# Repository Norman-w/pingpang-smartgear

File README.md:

# 乒乓智配 · PingPang SmartGear

乒乓球训练与比赛相关的智能辅助装备、配件及识别系统。

## 裸激光可调夹座首样

新增左侧十路裸激光方案：每颗光头装入独立球面夹筒，以两颗斜向螺钉微调，整排沿用原球头粗调。调整时从头套编号孔进入，邻近光头和盖件保持安装；预览页提供[原位调节演示与夹座特写](hardware/cad/preview/?view=laser)。尺寸暂按 Ø6×12 mm，实体适配和光路精度待实测。

设计、装配和独立 STL 包见[小夹座说明](docs/laser-micro-mount-v0.1.zh-CN.md)。前盖已加深、加宽并恢复完整弧形侧壁；新前后盖、承载条、底盖及底部柔性垫配套使用。预览支持围绕鼠标缩放和各倍率下平移。下文原 M6 电子与打印资料保留作参考，不表示其电路已经适配裸激光。

[接收端配套外壳](docs/receiver-mount-v0.1.zh-CN.md)也已同步扩大，提供独立五件打印包和右侧特写；内部接收元件选择尚未确认。

## 当前项目

当前机械主线是一套免打孔的内置式球网支架：左右夹体固定在球台边缘，网布直接装入两侧立柱，网端附近各有一个 PVDF 振动传感器；左右各十路 M6 发射/接收器件用于过网高度/事件采集，电子系统由 ESP32-S3 主控和独立 M6 接收载板组成。

当前阶段已经完成：

- OpenSCAD 统一机械参数源、完整装配、爆炸和真实截面诊断；
- C 形夹按 y=0 分型为两半；承载发射/接收头的斜立柱另分为下段和顶部 `30 mm` 上段，分型处用公母定位键和四枚 M3×40 连接；网布侧边使用独立圆柱插杆，不再使用外侧矩形网夹；立柱从黄灰交界 `z=16 mm` 延伸至 `z=260.5 mm`，不向下插入 C 形座；网布/圆柱插杆功能区仍为 `z=16…168.5 mm`；
- 网布的 `3 mm` 过道，以及球网空心边套和 `Ø10 mm` 圆柱插杆；插杆先穿过网布边套，再沿原门洞轴线从 x 侧推入下段侧开接收腔，门洞宽度保持历史 `15.2 mm`，立柱分型位于顶部下 `30 mm`，网顶不设置轨道；
- ESP32 主控、电池、电源保护、接收/发射/UI 子板的 KiCad/Atopile 交接包；
- 板框、安装孔、梯形腔、y+ 一体式 UI 填平固定板和电子件的统一 fit report；
- 当前 `41` 个正式机械 STL，以及 `256 mm` 打印床 `7` 张板、`41` 件、`0` 件超尺寸的几何拼盘；斜立柱下段/绿色载体采用实际三轴斜放，上段按平放姿态打印。

仍未由文件替代的工作包括：PCB 铜箔/器件生产释放和电气波形、真实网布与 M6 SKU 实测、立柱与 C 夹的打印配合及 PETG 承力、盒盖实际贴合、切片/G-code、首层和实物装配联调。

网端安装规则：先把球网侧边空心布套套到一根 `Ø10 mm × 152.5 mm` 圆柱插杆上，再沿原门洞轴线从 x 侧推入下段侧开接收腔，最后安装上段把插杆封在立柱内；拆卸按相反顺序进行。固定 C 夹两半除网布过道外保持实心，立柱底面与 `z=16 mm` 黄灰交界共面，分型在顶部下 `30 mm`，上段与下段用公母键和四枚 M3×40 连接；下段从承托面起做 `35×58 mm → 28×38 mm` 连续实心渐变，以上保持 `28×38 mm`。

这里的“齐平”仅表示一体式 UI 填平固定板和 M6 盖件装配后没有明显错台或松动，不宣称 IP 防水等级。

## 仓库结构

```text
docs/       需求、技术方案、测量定义和测试记录
hardware/   机械 CAD、电子板、BOM、打印和装配资料
firmware/   设备控制器、传感器采集和通信固件
vision/     球体检测、轨迹估计、过网高度计算
software/   标定工具、调试界面和训练/比赛数据接口
```

## 入口文档

- [硬件工程说明](hardware/README.md)
- [OpenSCAD 机械主线](hardware/cad/README.md)
- [打印清单](hardware/cad/print-manifest.zh-CN.md)
- [ESP32 主控与 1S 电源首样板](hardware/electronics/esp32-control-v0.1/README.zh-CN.md)
- [统一电子系统干涉/打印自证报告](hardware/electronics/fit-report-v0.2.md)
- [Atopile 系统接口合同](hardware/electronics/atopile/README.zh-CN.md)
- [系统机械—电气接口合同](hardware/electronics/system-packaging-v0.2.zh-CN.md)
- [M6 阵列设计说明](docs/m6-optical-array-design-v0.1.zh-CN.md)
- [首样采购与装配清单](hardware/first-article-bom.zh-CN.md)

## 设计原则

1. 先建立可测量、可追溯的机械和高度基准。
2. 机械、电子和识别链路分层，任何一层未实测时保持 `pending/unknown`。
3. 以装配、干涉、通道数量和实物波形共同放行，不以“能编译”代替接板通过。
4. 所有打印包必须能追溯到参数源、清单、包围盒和封闭拓扑摘要。

本项目当前面向训练、实验和产品研发；未经重复性、环境适应性和规则符合性验证的版本，不作为正式比赛裁判依据。

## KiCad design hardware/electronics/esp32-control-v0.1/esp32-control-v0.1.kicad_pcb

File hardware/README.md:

# 硬件工程

这里放置内置式球网支架、两侧 M6 发射/接收阵列、网端 PVDF 传感器、ESP32 主控、子板、电池和装配资料。

新增的左侧裸激光可调小夹座见[结构与装配说明](../docs/laser-micro-mount-v0.1.zh-CN.md)。单颗特写、原位调节演示与整排共用 SCAD 导出的模型，工具从编号孔进入，邻居和后盖保持固定。输出位于 `cad/exports/laser-micro-mount-v0.1/`；加大前腔的新前盖、新承载条、后盖、底盖与底部柔性垫成套使用，原 M6 电气资料仅供接口参考。

右侧也已同步[接收端外壳](../docs/receiver-mount-v0.1.zh-CN.md)，输出为 `cad/exports/receiver-mount-v0.1/`；内部元件仍为原M6接口参考，待确认接收器后适配固定座。

## 当前硬件拆分

- [`cad/`](cad/)：参数化 OpenSCAD 机械源、完整装配/爆炸/剖切预览、正式 STL 导出和 256 mm 打印拼盘；
- [`electronics/`](electronics/)：ESP32-S3 主控板、M6 接收载板、发射端内置电源子板、UI 子板、Atopile 接口合同、3D 板模型和统一壳内干涉报告；
- [`first-article-bom.zh-CN.md`](first-article-bom.zh-CN.md)：首样采购和实物放行边界；
- [`../docs/m6-optical-array-design-v0.1.zh-CN.md`](../docs/m6-optical-array-design-v0.1.zh-CN.md)：M6 阵列和安装基准。

电子系统的机械—电气合同见 [`electronics/system-packaging-v0.2.zh-CN.md`](electronics/system-packaging-v0.2.zh-CN.md)。其中已给出母板、接收/发射/UI 子板、端子化线束、电池仓、USB-C、按钮、屏幕预留、扬声器/蜂鸣器、指示灯和梯形腔的统一坐标。主控与 1S 电源首样板见 [`electronics/esp32-control-v0.1/`](electronics/esp32-control-v0.1/)，M6 接收载板和发射端电源子板见 [`electronics/daughter-boards-v0.2/`](electronics/daughter-boards-v0.2/)。

## 当前机械结构

网顶不设置轨道。网布侧边空心布套先套到 `Ø10 mm × 152.5 mm` 圆柱插杆，再把这套组件从球台中心侧穿过立柱下段的连续 `3 mm` 网布过道，沿原门洞轴线从 x 侧推入下段的侧开接收腔；安装上段后封住插入口。斜立柱在顶部下 `30 mm` 分成下段和可替换上段，两段用公母定位键和四枚 M3×40 自攻钉连接。网端附近左右各一个 PVDF 振动传感器，与网架保留 `18 mm` 横向净距。

C 形夹按 y=0 分型为 `clamp_body_half_user` 与 `clamp_body_half_opponent` 两半，斜立柱和绿色载体则由 `post_clamp_carrier_lower`、`post_clamp_carrier_upper` 两件打印；固定夹半体除网布 `3 mm` 过道和侧开接收腔外保持实心。立柱底面在 C 夹黄灰交界 `z=16 mm` 共面，分型位于顶部下 `30 mm`，上段带公母键、四枚 M3×40 连接孔和中心 M8×1.25 攻丝座；网布/圆柱插杆功能区仍只到 `z=168.5 mm`。网端装配不使用矩形卡夹、keeper 或竖直盲孔：先把边套套在 Ø10 圆柱上，再沿 x 方向推入下段侧开接收腔，最后合上上段。球头下端直接拧入上段中心座，四枚立柱连接螺丝只属于立柱上下段。

盒盖、压合边和接口以“装配后严丝合缝、无明显贯穿缝”为目标；这里不宣称防水等级。真实网布、螺纹、张力、线缆弯曲和夹体耐久必须用首样实测。

## 打印状态

当前正式机械包以 [`cad/print-manifest.zh-CN.md`](cad/print-manifest.zh-CN.md) 和 [`cad/exports/desktop-clamp-one-side-x1c-v0.7-split-c-scheme/manifest.json`](cad/exports/desktop-clamp-one-side-x1c-v0.7-split-c-scheme/manifest.json) 为准：`41` 个 STL。256 mm 打印床拼盘见 [`cad/exports/desktop-clamp-one-side-x1c-v0.7-split-c-scheme/print-platter-256/manifest.json`](cad/exports/desktop-clamp-one-side-x1c-v0.7-split-c-scheme/print-platter-256/manifest.json)：`7` 张板、`41` 个已排版、`0` 个超尺寸件；斜立柱下段/绿色载体使用实际三轴斜放，上段按分型面平放姿态打印。旧整高 C 夹、电子腔底盖/连续垫、网夹分体、套筒和内芯不再属于当前清单；旧矩形卡条与 keeper 已移除，当前为独立 Ø10 mm 圆柱插杆和下段侧开接收腔。

立柱上下段连接螺丝当前按普通盘头或低矮圆头 `M3×40` 自攻钉采购；结构没有 90° 沉头窝，也不使用台阶肩螺丝。这是 CAD 包络/封闭 STL/排版证据，不是已切片、已生成 G-code 或已完成实物打印的证明。

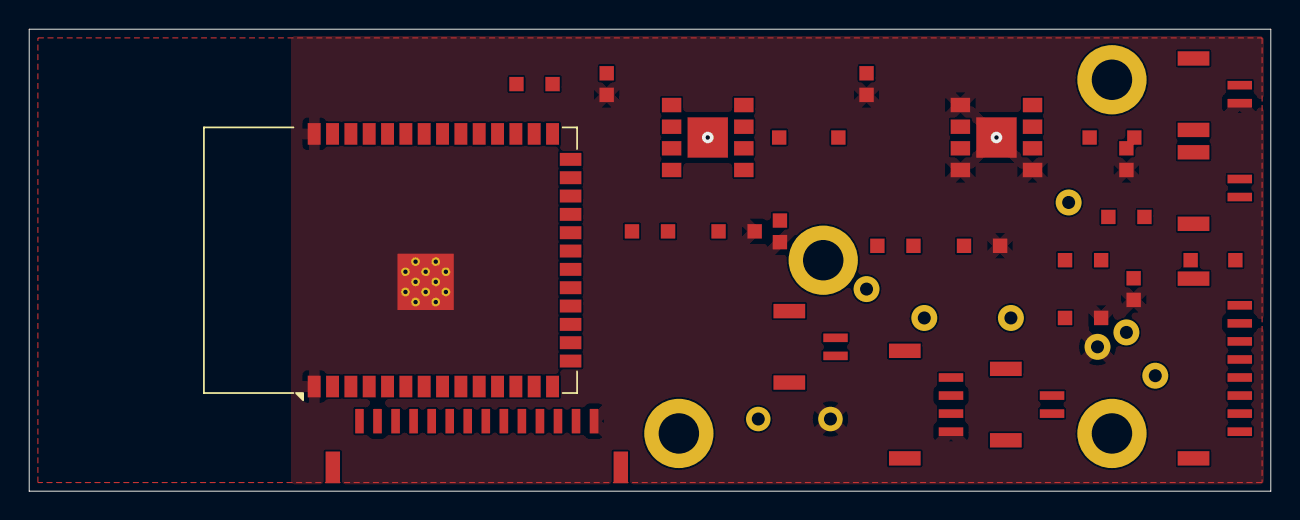
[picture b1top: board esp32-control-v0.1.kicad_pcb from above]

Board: 2 copper layers, 86.0 x 32.0 mm, 38 parts (0 on the bottom side), 34 nets, no tracks yet.

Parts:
C1: 100n BAT_SENSE
C2: 22u BAT
C3: 10u VBUS
C4: 22u SYS5V
C5: 10u 3V3
C6: 100n BUCK_EN
D1: GREEN STATUS
D2: TVS 33V SENSOR
F1: PTC 1.1A
F2: PTC SENSOR
H1, H2, H3, H4: M2.5 NPTH
J2: MX1.25_PROTECTED_1S_BAT
J3: MX1.25_SENSOR_10-30V_IN
J4: MX1.25_M6_CARRIER_HOST
J5: MX1.25_PVDF_ADC_AUX
J6: MX1.25_PVDF_CMP_AUX_DNP
J7: MX1.25_UI_PANEL_LOCK_14P_CHARGE
J8: MX1.25_M6_SENSOR_RAIL_LINK
L1: 2.2uH BOOST XFL4020
L2: 2.2uH BUCK XFL3012
R5: 1M BAT_TOP
R6: 1M BAT_BOTTOM
R7: 100k BUCK_EN
R8: 1k CHARGE_LED
SW1: IP5305 KEY
TP1, TP2, TP3, TP4, TP5, TP6, TP7: TEST_POINT
U1: ESP32-S3-WROOM-1-N16R8; ESP32-S3-WROOM-1
U2: IP5305T-HSOP8-1EP
U3: TPS62162-QFN8-EP

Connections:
3v3: C5.1, J4.1, J7.1, L2.2, TP4.1, U1.2, U3.6
bat_p: C2.1, J2.1, R5.1, TP1.1, U2.6
bat_sense: C1.1, R5.2, R6.1, TP2.1, U1.17
boost_sw: L1.1, U2.7
buck_en: C6.1, R7.2, U3.3
buck_sw: L2.1, U3.7
carrier_cs_n: J4.6, U1.21
carrier_irq_n: J4.7, TP6.1, U1.22
carrier_miso: J4.5, U1.20
carrier_mosi: J4.4, U1.19
carrier_reset_n: J4.8, U1.5
carrier_sck: J4.3, U1.18
gnd: C1.2, C2.2, C3.2, C4.2, C5.2, C6.2, D1.2, J2.2, J4.2, J5.2, J5.4, J7.2, J7.14, R6.2, SW1.2, TP5.1, U1.1, U1.40, U1.41, U2.9, U3.1, U3.4, U3.5, U3.9
led_charge: R8.1, U2.2
power_key: SW1.1, U2.5
pvdf_adc_l: J5.1, U1.39
pvdf_adc_r: J5.3, U1.38
sensor_ext: F2.1, J3.1
sensor_fused: D2.1, F2.2, J8.1, TP7.1
sensor_gnd: D2.2, J3.2, J8.2
status_led: D1.1, R8.2
sys_5v: C4.1, L1.2, R7.1, TP3.1, U2.8, U3.2
ui_btn_mode: J7.6, U1.4
ui_btn_start: J7.5, U1.16
ui_buzzer: J7.7, U1.13
ui_led_battery: J7.12, U1.23
ui_led_status: J7.11, U1.12
ui_scl: J7.4, U1.9
ui_sda: J7.3, U1.10
ui_spk_bclk: J7.8, U1.7
ui_spk_dout: J7.10, U1.11
ui_spk_ws: J7.9, U1.8
usb_vbus: F1.1, J7.13
vbus_limited: C3.1, F1.2, U2.1

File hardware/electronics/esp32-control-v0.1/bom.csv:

ref,qty,value,role,status,notes
U1,1,ESP32-S3-WROOM-1-N16R8,主控,候选,按模块官方 land pattern 与 N16R8 OPI 限制复核
U2,1,IP5305T-HSOP8-1EP,1S 充电/5V 升压,候选,按现有 SmartPaddle 电源架构复核 VIN/BAT/SW/VOUT/EP
U3,1,TPS62162-QFN8-EP,3V3 降压,候选,固定 3.3V；FB 接地；PG 保留测试点
J2,1,MX1.25_PROTECTED_1S_LOCK_2P,受保护 1S 电池,候选,物理节距锁定 1.25 mm；禁止裸电芯；确认极性与线束防呆
J3,1,MX1.25_SENSOR_10-30V_IN,外部 M6 电源,首样,物理节距锁定 1.25 mm；pin2 为 sensor_gnd/0V_SENSOR，与 MCU GND 分离
J4,1,MX1.25_M6_CARRIER_HOST_8P,STM32G031 载板,接口已落板,物理节距锁定 1.25 mm；3V3/GND/SCK/MOSI/MISO/CS/IRQ/RESET
J5,1,MX1.25_PVDF_ADC_AUX_4P,PVDF ADC,辅助,物理节距锁定 1.25 mm；GPIO1/2；AFE 仍待设计
J6,1,MX1.25_PVDF_CMP_AUX_DNP_2P,PVDF 比较器辅助,不装,物理节距锁定 1.25 mm；GPIO14 给载板 IRQ；避免隐式复用
J7,1,MX1.25_UI_PANEL_LOCK_14P_CHARGE,UI 子板 14 芯对插,候选,物理节距锁定 1.25 mm；1-12 为 UI 控制，13/14 为 Type-C VBUS/GND；按真实锁扣座核对
J8,1,MX1.25_M6_SENSOR_RAIL_LINK_2P,接收载板传感器电源,候选,物理节距锁定 1.25 mm；pin1/pin2 映射 sensor_fused/sensor_gnd 到接收载板 J_PWR
F1,1,PTC 1.1A,UI Type-C 充电输入限流,候选,实测 UI 面板 Type-C 输入峰值和温升
F2,1,PTC SENSOR,传感器电源保护,候选,电流按 M6 实物确认
D2,1,TVS 33V SENSOR,传感器电源 TVS,候选,型号随外部 10–30V 瞬态记录冻结
L1,1,2.2uH BOOST XFL4020,IP5305T 升压电感,候选,按 U2 推荐布局/饱和电流复核
L2,1,2.2uH BUCK XFL3012,TPS62162 降压电感,候选,按 U3 推荐布局/电流复核
R5,1,1M BAT_TOP,电池分压上臂,候选,GPIO9 sense
R6,1,1M BAT_BOTTOM,电池分压下臂,候选,GPIO9 sense
R7,1,100k BUCK_EN,降压使能上拉,候选,与 C6 形成首样启动控制
R8,1,1k CHARGE_LED,充电指示限流,候选,LED 电流实测
C1,1,100n BAT_SENSE,电池采样滤波,候选,靠近 ESP32 ADC
C2,1,22u BAT,电池去耦,候选,按 IP5305T 推荐值复核
C3,1,10u VBUS,输入去耦,候选,靠近 U2 VIN
C4,1,22u SYS5V,升压输出去耦,候选,靠近 U2 VOUT
C5,1,10u 3V3,3V3 输出去耦,候选,靠近 U3/ESP32
C6,1,100n BUCK_EN,使能滤波,候选,按 EN 启动波形复核
D1,1,GREEN STATUS,充电/电源指示,候选,LED1 路径
SW1,1,IP5305 KEY,电源按键,候选,确认 IP5305T KEY 时序

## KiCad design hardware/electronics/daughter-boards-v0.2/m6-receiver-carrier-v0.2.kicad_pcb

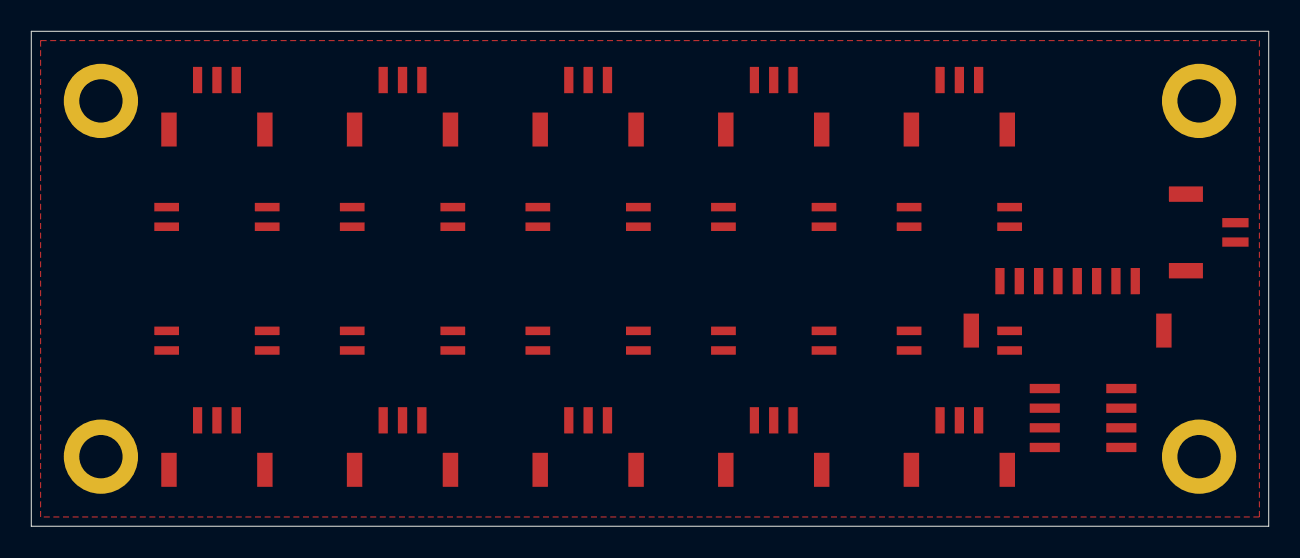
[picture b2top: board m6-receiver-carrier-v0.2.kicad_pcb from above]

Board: 2 copper layers, 80.0 x 32.0 mm, 27 parts (0 on the bottom side), 28 nets, no tracks yet.

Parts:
H1, H2, H3, H4: M2.5 NPTH
J_HOST: MX1.25_MOTHER_HOST_LOCK_8P
J_PWR: MX1.25_SENSOR_RAIL_LOCK_2P
J_RX00, J_RX01, J_RX02, J_RX03, J_RX04, J_RX05, J_RX06, J_RX07, J_RX08, J_RX09: MX1.25_LOCK_3P_RX
U_MCU: STM32G031_PLACEHOLDER
U_OP00, U_OP01, U_OP02, U_OP03, U_OP04, U_OP05, U_OP06, U_OP07, U_OP08, U_OP09: OPTO_PLACEHOLDER

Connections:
3v3: J_HOST.1, U_MCU.7, U_OP00.3, U_OP01.3, U_OP02.3, U_OP03.3, U_OP04.3, U_OP05.3, U_OP06.3, U_OP07.3, U_OP08.3, U_OP09.3
carrier_cs_n: J_HOST.6, U_MCU.4
carrier_irq_n: J_HOST.7, U_MCU.5
carrier_miso: J_HOST.5, U_MCU.3
carrier_mosi: J_HOST.4, U_MCU.2
carrier_reset_n: J_HOST.8, U_MCU.6
carrier_sck: J_HOST.3, U_MCU.1
gnd: J_HOST.2, U_MCU.8, U_OP00.4, U_OP01.4, U_OP02.4, U_OP03.4, U_OP04.4, U_OP05.4, U_OP06.4, U_OP07.4, U_OP08.4, U_OP09.4
rx00_gnd: J_RX00.2, U_OP00.2
rx00_sig: J_RX00.3, U_OP00.1
rx01_gnd: J_RX01.2, U_OP01.2
rx01_sig: J_RX01.3, U_OP01.1
rx02_gnd: J_RX02.2, U_OP02.2
rx02_sig: J_RX02.3, U_OP02.1
rx03_gnd: J_RX03.2, U_OP03.2
rx03_sig: J_RX03.3, U_OP03.1
rx04_gnd: J_RX04.2, U_OP04.2
rx04_sig: J_RX04.3, U_OP04.1
rx05_gnd: J_RX05.2, U_OP05.2
rx05_sig: J_RX05.3, U_OP05.1
rx06_gnd: J_RX06.2, U_OP06.2
rx06_sig: J_RX06.3, U_OP06.1
rx07_gnd: J_RX07.2, U_OP07.2
rx07_sig: J_RX07.3, U_OP07.1
rx08_gnd: J_RX08.2, U_OP08.2
rx08_sig: J_RX08.3, U_OP08.1
rx09_gnd: J_RX09.2, U_OP09.2
rx09_sig: J_RX09.3, U_OP09.1

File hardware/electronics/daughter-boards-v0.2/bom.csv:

board,ref,qty,value,role,status,notes
m6-receiver-carrier-v0.2,U_OP00..U_OP09,10,opto-isolator + input resistor,十路 NPN 隔离前端,候选,按 M6 输出极性/电流和 STM32 输入阈值冻结
m6-receiver-carrier-v0.2,J_RX00..J_RX09,10,MX1.25_LOCK_3P_RX,十路接收器三芯对插,候选,线束汇聚后插入；按线径和插拔空间核对真实 MX1.25 封装
m6-receiver-carrier-v0.2,J_HOST,1,MX1.25_MOTHER_HOST_LOCK_8P,母板逻辑接口,候选,3V3/GND/SPI/IRQ/RESET；物理节距锁定 1.25 mm
m6-receiver-carrier-v0.2,J_PWR,1,MX1.25_SENSOR_RAIL_LOCK_2P,接收器外部电源接口,候选,与母板逻辑线分开；物理节距锁定 1.25 mm
m6-receiver-carrier-v0.2,U_MCU,1,STM32G031_PLACEHOLDER,十路边沿采集 MCU,候选,占位封装；最终按独立载板方案冻结
emitter-power-v0.2,J_BAT,1,MX1.25_PROTECTED_1S_LOCK_2P,内置受保护 1S 电池接口,候选,物理节距锁定 1.25 mm；禁止裸电芯；需防呆/锁扣
emitter-power-v0.2,J_EXT,1,MX1.25_EXT_TX_10-30V_2P_CURRENT_GATE,发射端外接后备电源,候选,MX1.25 物理接口；额定电流/端子温升仍需核对，不与电池裸并联
emitter-power-v0.2,U_BOOST,1,TX_BOOST_CURRENT_RATED_PLACEHOLDER,发射端升压/限流,候选,按十路同时点亮电流和温升冻结
emitter-power-v0.2,F_TX,1,PTC_OR_FUSE,发射端过流保护,候选,按内置电池/外部输入分别核算
emitter-power-v0.2,D_TVS,1,TVS_BY_MODULE,发射端输入瞬态保护,候选,外部输入路径按 10–30 V 边界复核
emitter-power-v0.2,J_TX_A/J_TX_B,2,MX1.25_TX_A/B_10P,十路发射器两芯线束,候选,TX00..TX04 与 TX05..TX09 各 10 芯；不使用 2.54 mm 或错误 1.27 mm 20P 模型
ui-panel-v0.2,J_MOTHER,1,MX1.25_MOTHER_UI_LOCK_14P_CHARGE,母板 UI 对插,候选,物理节距锁定 1.25 mm；13/14 脚带回 Type-C VBUS/GND；核对真实锁扣座
ui-panel-v0.2,J_OLED,1,MX1.25_I2C_OLED_FPC_4P,0.96 英寸 OLED 排线接口,候选,屏幕独立安装；物理节距锁定 1.25 mm；盖板透明窗/压框
ui-panel-v0.2,SW_START/SW_MODE,2,SW_SPST_TS-1088-xR020,PCB 直装 START/MODE 贴片按键,候选,3.9×3.0×2.0 mm 两脚 SMD；面框内置 1.6 mm plunger 直接顶按键
ui-panel-v0.2,D_STATUS/D_BAT,2,LED_0603_1608Metric_GREEN/YELLOW,PCB 直装状态/电池 0603 LED,候选,单色 0603 顶发光；面框开 2.2 mm 直孔；不引入 WS2812/RGB 新走线
ui-panel-v0.2,J_BUZ,1,MX1.25_BUZZER_LOCK_2P,蜂鸣器接口,候选,物理节距锁定 1.25 mm；盖板声学膜/防护网
ui-panel-v0.2,J_SPK,1,MX1.25_I2S_SPEAKER_LOCK_5P,扬声器 I2S 接口,候选,物理节距锁定 1.25 mm；按峰值电流/声学窗口核对
ui-panel-v0.2,J_USB_PANEL,1,USB_C_Receptacle_GCT_USB4105-xx-A_16P_TopMnt_Horizontal,PCB 直装 Type-C 充电插座,候选,16 针 KiCad 库模型随板 STL 导出并旋转到 y+ 面板法向；仅 VBUS/GND/CC 使用，D+/D−/SBU 留空；端口穿过面框并配硅胶帽；待首样冻结具体厂家料号
ui-panel-v0.2,R_CC1/R_CC2,2,R_0603_1608Metric 5k1,Type-C CC 下拉,候选,CC1/CC2 各一颗 5.1 kΩ Rd 到 GND

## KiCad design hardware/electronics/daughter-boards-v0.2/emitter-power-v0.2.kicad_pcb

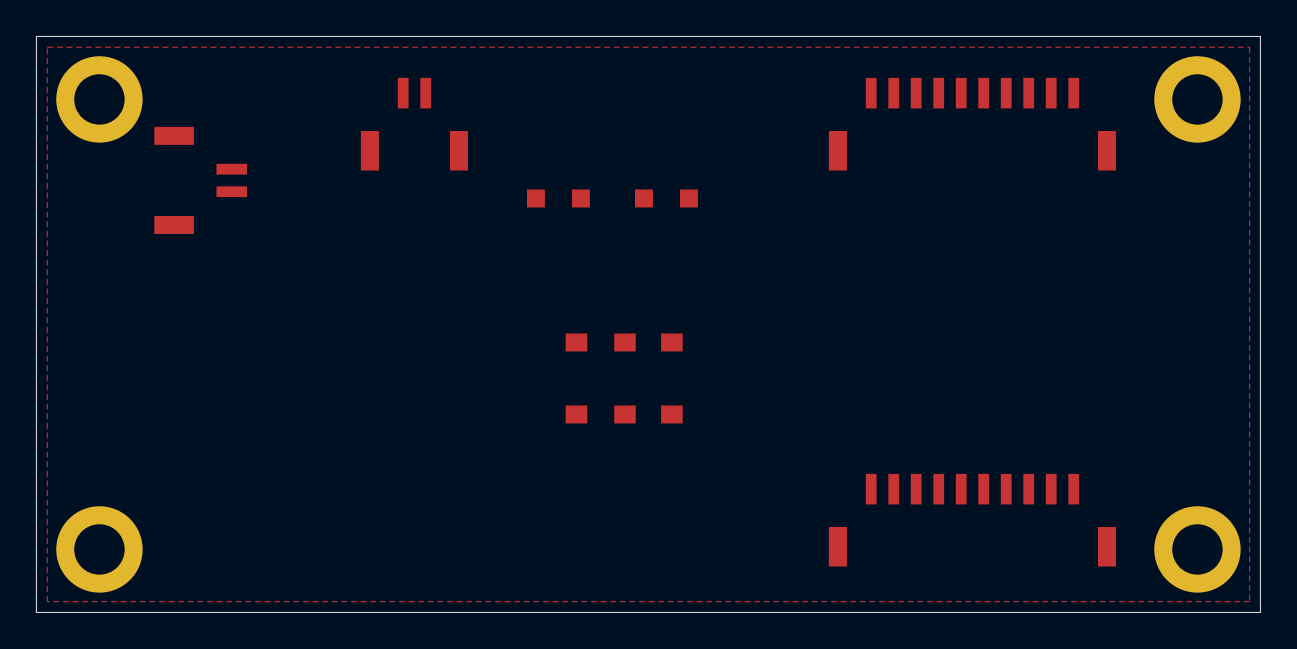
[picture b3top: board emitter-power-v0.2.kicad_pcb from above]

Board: 2 copper layers, 68.0 x 32.0 mm, 11 parts (0 on the bottom side), 5 nets, no tracks yet.

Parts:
D_TVS: TVS_BY_MODULE
F_TX: PTC_OR_FUSE
H1, H2, H3, H4: M2.5 NPTH
J_BAT: MX1.25_PROTECTED_1S_LOCK_2P
J_EXT: MX1.25_EXT_TX_10-30V_2P_CURRENT_GATE
J_TX_A: MX1.25_TX_A_10P
J_TX_B: MX1.25_TX_B_10P
U_BOOST: TX_BOOST_CURRENT_RATED_PLACEHOLDER

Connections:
bat_gnd: J_BAT.2, U_BOOST.2
bat_p: J_BAT.1, U_BOOST.1
ext_tx_gnd: D_TVS.2, J_EXT.2
ext_tx_in: F_TX.1, J_EXT.1
tx_rail: D_TVS.1, F_TX.2, U_BOOST.3

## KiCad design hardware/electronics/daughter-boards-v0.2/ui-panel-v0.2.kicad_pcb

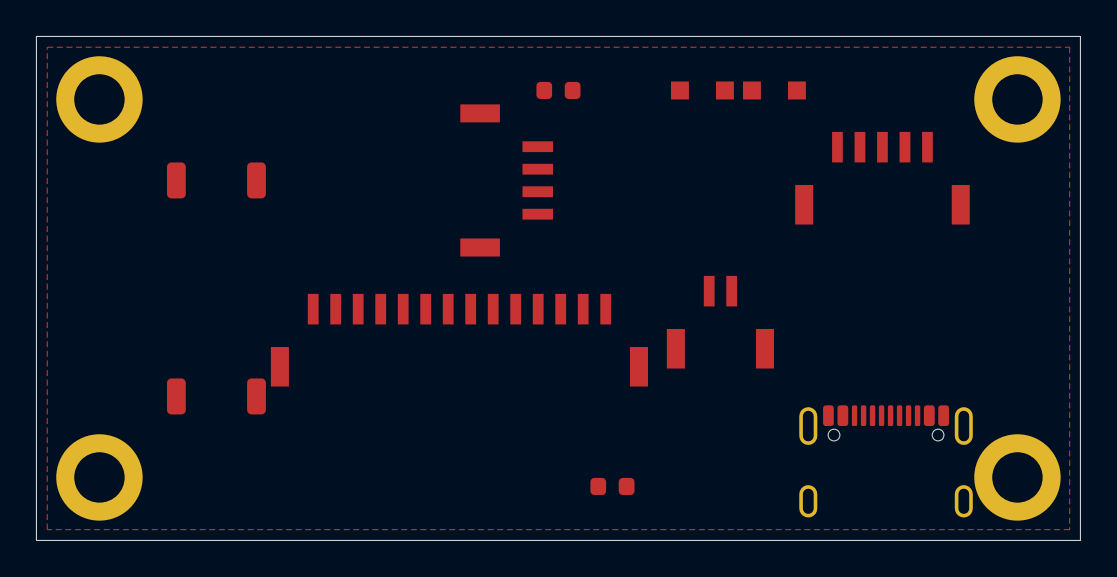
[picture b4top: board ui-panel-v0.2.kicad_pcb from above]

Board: 2 copper layers, 58.0 x 28.0 mm, 15 parts (0 on the bottom side), 15 nets, no tracks yet.

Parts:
D_BAT: LED_BATTERY_0603_YELLOW; LED_0603_1608Metric
D_STATUS: LED_STATUS_0603_GREEN; LED_0603_1608Metric
H1, H2, H3, H4: M2.5 NPTH
J_BUZ: MX1.25_BUZZER_LOCK_2P
J_MOTHER: MX1.25_MOTHER_UI_LOCK_14P_CHARGE
J_OLED: MX1.25_I2C_OLED_FPC_4P
J_SPK: MX1.25_I2S_SPEAKER_LOCK_5P
J_USB_PANEL: USB-C_VERTICAL_CHARGE_ONLY; USB_C_Receptacle_GCT_USB4105-xx-A_16P_TopMnt_Horizontal
R_CC1: 5k1 USB-C CC1 Rd
R_CC2: 5k1 USB-C CC2 Rd
SW_MODE: SEALED_SMD_TACTILE_MODE; SW_SPST_TS-1088-xR020
SW_START: SEALED_SMD_TACTILE_START; SW_SPST_TS-1088-xR020

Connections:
3v3: J_MOTHER.1, J_OLED.1, J_SPK.4
cc1: J_USB_PANEL.A5, R_CC1.1
cc2: J_USB_PANEL.B5, R_CC2.1
gnd: D_BAT.2, D_STATUS.2, J_BUZ.2, J_MOTHER.2, J_MOTHER.14, J_OLED.2, J_SPK.5, J_USB_PANEL.A1, J_USB_PANEL.A12, J_USB_PANEL.B1, J_USB_PANEL.B12, J_USB_PANEL.SH, R_CC1.2, R_CC2.2, SW_MODE.2, SW_START.2
ui_btn_mode: J_MOTHER.6, SW_MODE.1
ui_btn_start: J_MOTHER.5, SW_START.1
ui_buzzer: J_BUZ.1, J_MOTHER.7
ui_led_battery: D_BAT.1, J_MOTHER.12
ui_led_status: D_STATUS.1, J_MOTHER.11
ui_scl: J_MOTHER.4, J_OLED.4
ui_sda: J_MOTHER.3, J_OLED.3
ui_spk_bclk: J_MOTHER.8, J_SPK.1
ui_spk_dout: J_MOTHER.10, J_SPK.3
ui_spk_ws: J_MOTHER.9, J_SPK.2
usb_vbus: J_MOTHER.13, J_USB_PANEL.A4, J_USB_PANEL.A9, J_USB_PANEL.B4, J_USB_PANEL.B9
